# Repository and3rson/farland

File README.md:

# farland
65C816-based single-board computer

# Schematic

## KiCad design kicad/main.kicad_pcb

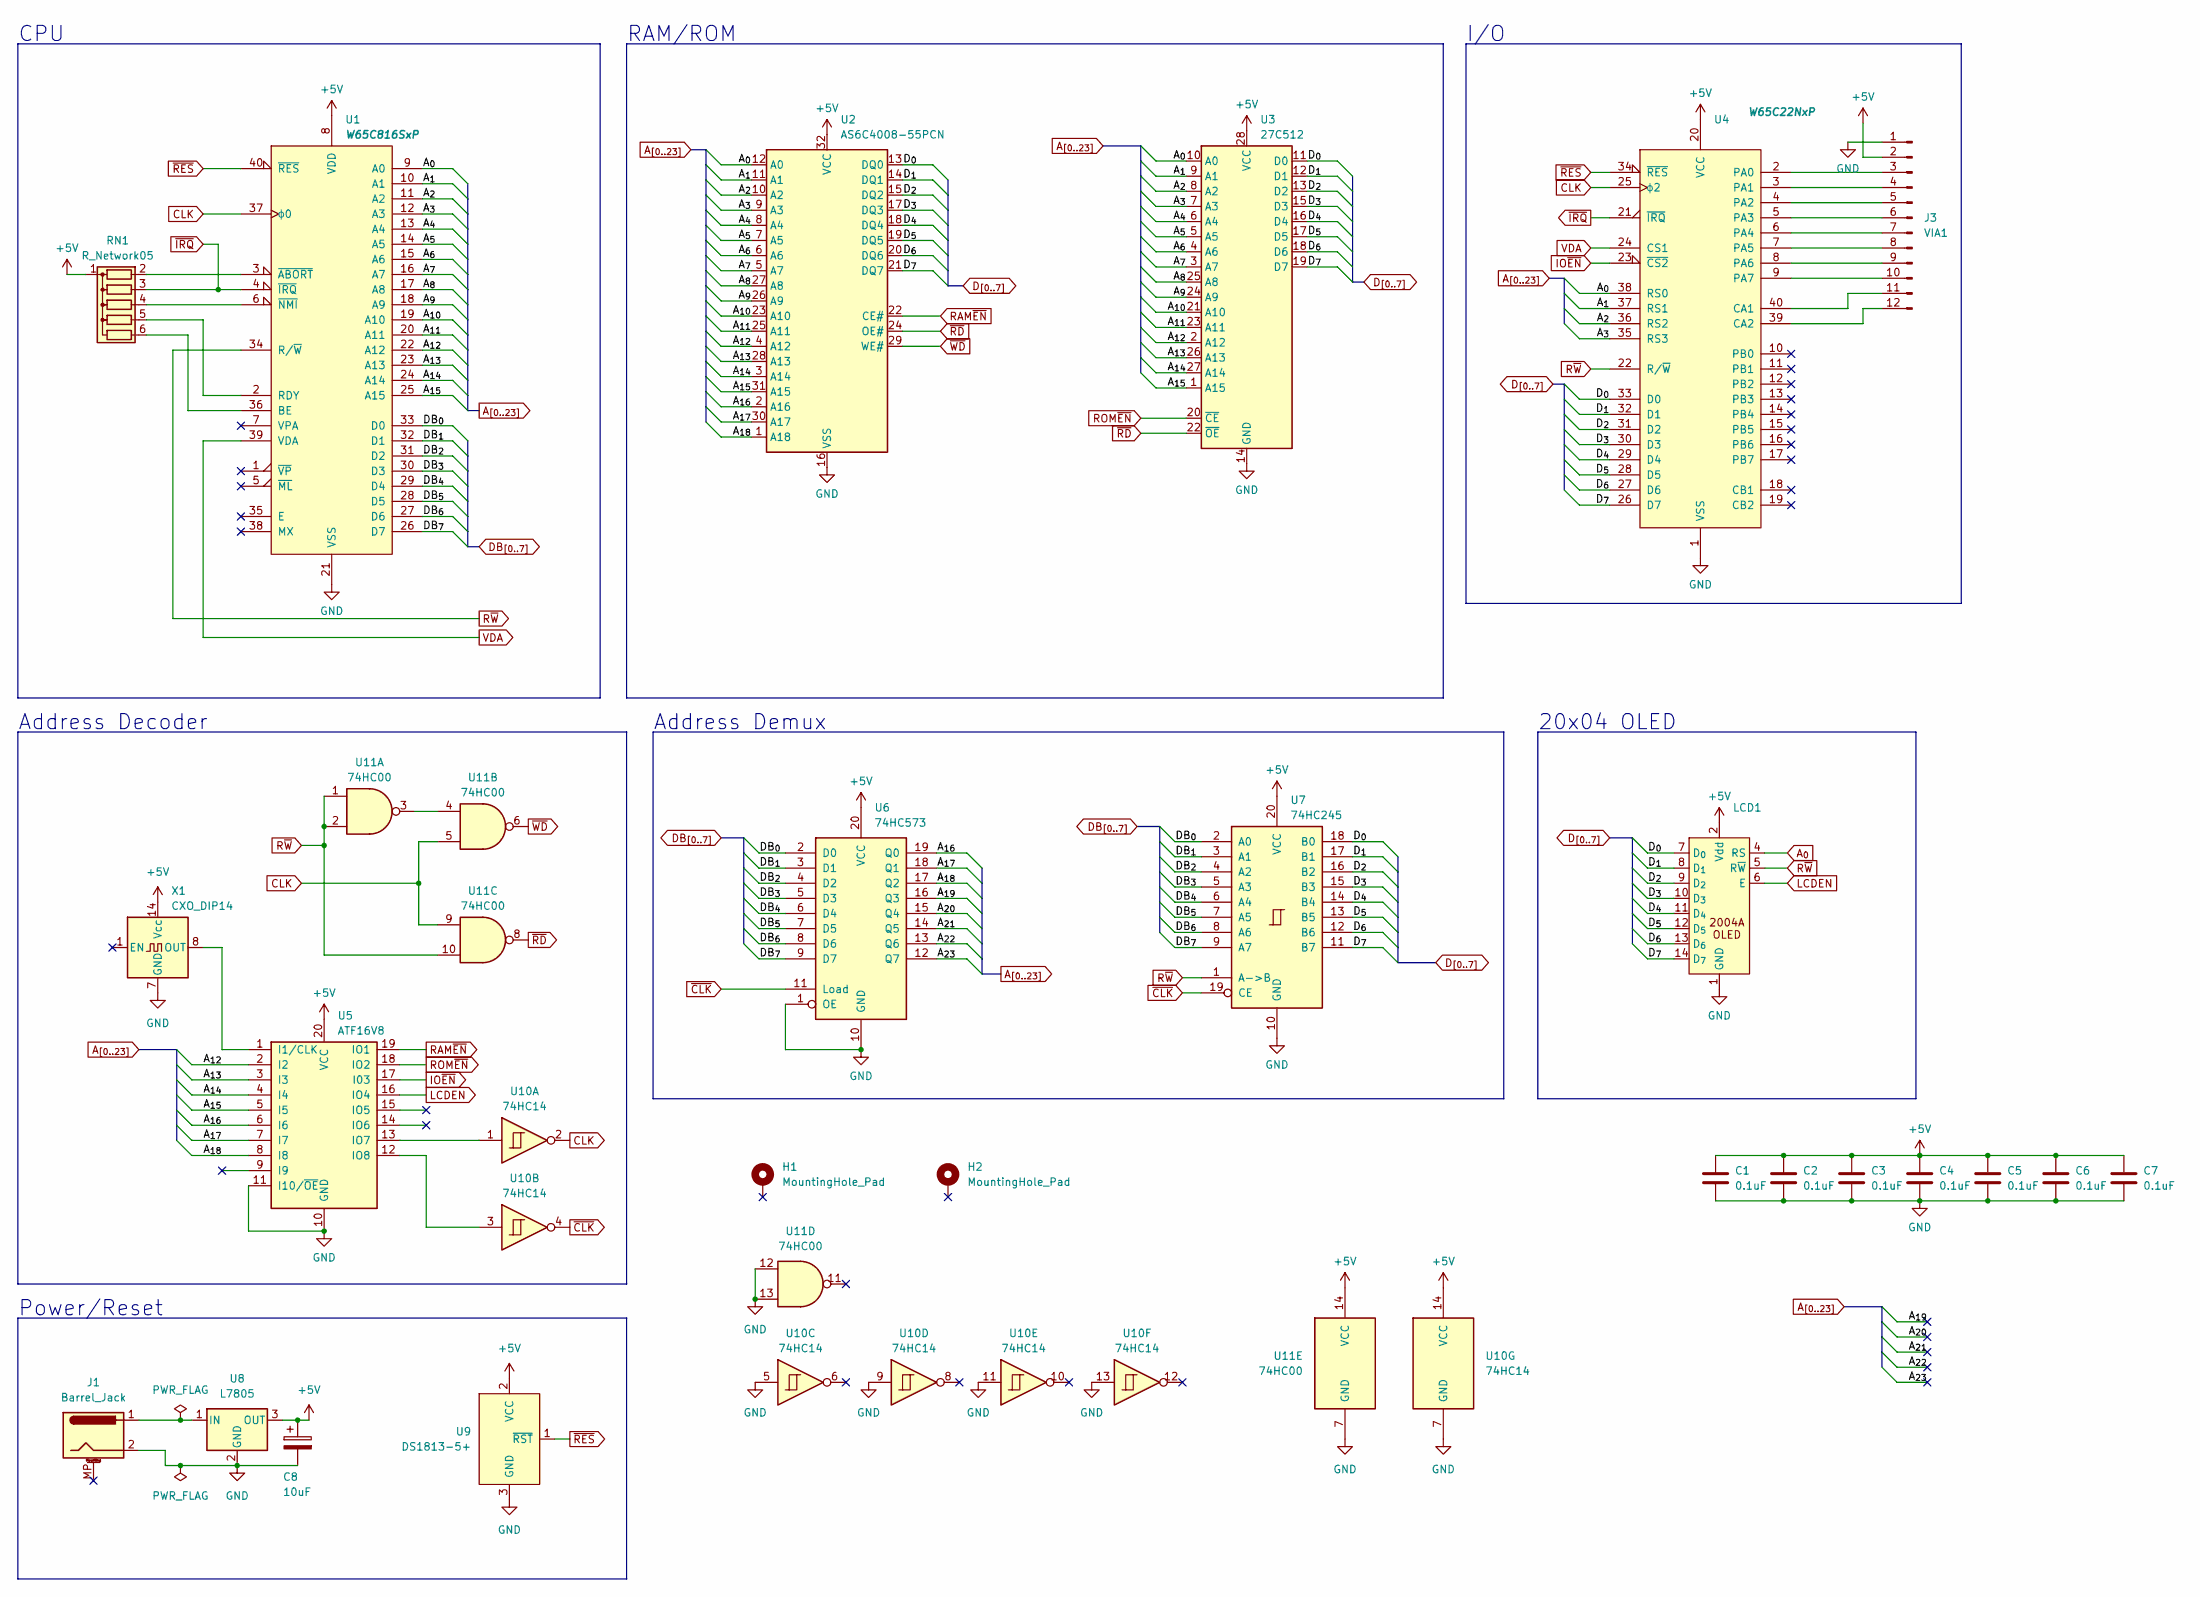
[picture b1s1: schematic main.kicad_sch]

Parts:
C1: 0.1uF; C_Disc_D3.0mm_W1.6mm_P2.50mm
C2, C3, C4: 0.1uF; C_Disc_VeryLong
C5, C6, C7: 0.1uF; C_Disc_Long
C8: 10uF; CP_Radial_D6.3mm_P2.50mm
H1, H2: MountingHole_Pad; MountingHole_2.5mm_Pad
J1: Barrel_Jack; BarrelJack_Wuerth_6941xx301002
J3: VIA1; PinHeader_1x12_P2.54mm_Vertical
LCD1: 2004A-OLED
RN1: R_Network05; R_Array_SIP6
U1: W65C816SxP; DIP-40_W15.24mm_Socket
U2: AS6C4008-55PCN; DIP-32_W15.24mm_Socket
U3: 27C512; ZIF28
U4: W65C22NxP; DIP-40_W15.24mm_Socket
U5: ATF16V8; DIP-20_W7.62mm_Socket
U6: 74HC573; DIP-20_W7.62mm_Socket
U7: 74HC245; DIP-20_W7.62mm_Socket
U8: L7805; TO-220-3_Vertical
U9: DS1813-5+; TO-92
U10: 74HC14; DIP-14_W7.62mm_Socket
U11: 74HC00; DIP-14_W7.62mm_Socket
X1: CXO_DIP14; Oscillator_DIP-14

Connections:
+5V: C1.1, C2.1, C3.1, C4.1, C5.1, C6.1, C7.1, C8.1, J3.2, LCD1.2 (Vdd), RN1.1 (common), U1.8 (VDD), U2.32 (VCC), U3.28 (VCC), U4.20 (VCC), U5.20 (VCC), U6.20 (VCC), U7.20 (VCC), U8.3 (OUT), U9.2 (VCC), U10.14 (VCC), U11.14 (VCC), X1.14 (Vcc)
A_{0}: LCD1.4 (RS), U1.9 (A0), U2.12 (A0), U3.10 (A0), U4.38 (RS0)
A_{1}: U1.10 (A1), U2.11 (A1), U3.9 (A1), U4.37 (RS1)
A_{2}: U1.11 (A2), U2.10 (A2), U3.8 (A2), U4.36 (RS2)
A_{3}: U1.12 (A3), U2.9 (A3), U3.7 (A3), U4.35 (RS3)
A_{4}: U1.13 (A4), U2.8 (A4), U3.6 (A4)
A_{5}: U1.14 (A5), U2.7 (A5), U3.5 (A5)
A_{6}: U1.15 (A6), U2.6 (A6), U3.4 (A6)
A_{7}: U1.16 (A7), U2.5 (A7), U3.3 (A7)
A_{8}: U1.17 (A8), U2.27 (A8), U3.25 (A8)
A_{9}: U1.18 (A9), U2.26 (A9), U3.24 (A9)
A_{10}: U1.19 (A10), U2.23 (A10), U3.21 (A10)
A_{11}: U1.20 (A11), U2.25 (A11), U3.23 (A11)
A_{12}: U1.22 (A12), U2.4 (A12), U3.2 (A12), U5.2 (I2)
A_{13}: U1.23 (A13), U2.28 (A13), U3.26 (A13), U5.3 (I3)
A_{14}: U1.24 (A14), U2.3 (A14), U3.27 (A14), U5.4 (I4)
A_{15}: U1.25 (A15), U2.31 (A15), U3.1 (A15), U5.5 (I5)
A_{16}: U2.2 (A16), U5.6 (I6), U6.19 (Q0)
A_{17}: U2.30 (A17), U5.7 (I7), U6.18 (Q1)
A_{18}: U2.1 (A18), U5.8 (I8), U6.17 (Q2)
A_{19}: U6.16 (Q3)
A_{20}: U6.15 (Q4)
A_{21}: U6.14 (Q5)
A_{22}: U6.13 (Q6)
A_{23}: U6.12 (Q7)
CLK: U1.37 (ϕ0), U4.25 (ϕ2), U10.2, U11.5, U11.9
DB_{0}: U1.33 (D0), U6.2 (D0), U7.2 (A0)
DB_{1}: U1.32 (D1), U6.3 (D1), U7.3 (A1)
DB_{2}: U1.31 (D2), U6.4 (D2), U7.4 (A2)
DB_{3}: U1.30 (D3), U6.5 (D3), U7.5 (A3)
DB_{4}: U1.29 (D4), U6.6 (D4), U7.6 (A4)
DB_{5}: U1.28 (D5), U6.7 (D5), U7.7 (A5)
DB_{6}: U1.27 (D6), U6.8 (D6), U7.8 (A6)
DB_{7}: U1.26 (D7), U6.9 (D7), U7.9 (A7)
D_{0}: LCD1.7 (D_{0}), U2.13 (DQ0), U3.11 (D0), U4.33 (D0), U7.18 (B0)
D_{1}: LCD1.8 (D_{1}), U2.14 (DQ1), U3.12 (D1), U4.32 (D1), U7.17 (B1)
D_{2}: LCD1.9 (D_{2}), U2.15 (DQ2), U3.13 (D2), U4.31 (D2), U7.16 (B2)
D_{3}: LCD1.10 (D_{3}), U2.17 (DQ3), U3.15 (D3), U4.30 (D3), U7.15 (B3)
D_{4}: LCD1.11 (D_{4}), U2.18 (DQ4), U3.16 (D4), U4.29 (D4), U7.14 (B4)
D_{5}: LCD1.12 (D_{5}), U2.19 (DQ5), U3.17 (D5), U4.28 (D5), U7.13 (B5)
D_{6}: LCD1.13 (D_{6}), U2.20 (DQ6), U3.18 (D6), U4.27 (D6), U7.12 (B6)
D_{7}: LCD1.14 (D_{7}), U2.21 (DQ7), U3.19 (D7), U4.26 (D7), U7.11 (B7)
GND: C1.2, C2.2, C3.2, C4.2, C5.2, C6.2, C7.2, C8.2, J1.2, J3.1, LCD1.1 (GND), U1.21 (VSS), U2.16 (VSS), U3.14 (GND), U4.1 (VSS), U5.10 (GND), U5.11 (I10/~OE), U6.1 (OE), U6.10 (GND), U7.10 (GND), U8.2 (GND), U9.3 (GND), U10.5, U10.7 (GND), U10.9, U10.11, U10.13, U11.7 (GND), U11.12, U11.13, X1.7 (GND)
IO~EN: U4.23 (~CS2), U5.17 (I03)
LCDEN: LCD1.6 (E), U5.16 (IO4)
unnamed: J3.3, U4.2 (PA0)
unnamed: J3.4, U4.3 (PA1)
unnamed: J3.5, U4.4 (PA2)
unnamed: J3.6, U4.5 (PA3)
unnamed: J3.7, U4.6 (PA4)
unnamed: J3.8, U4.7 (PA5)
unnamed: J3.9, U4.8 (PA6)
unnamed: J3.10, U4.9 (PA7)
unnamed: J3.11, U4.40 (CA1)
unnamed: J3.12, U4.39 (CA2)
unnamed: RN1.2 (R1), U1.3 (~ABORT)
unnamed: RN1.4 (R3), U1.6 (~NMI)
unnamed: RN1.5 (R4), U1.2 (RDY)
unnamed: RN1.6 (R5), U1.36 (BE)
unnamed: U5.1 (I1/CLK), X1.8 (OUT)
unnamed: U5.13 (IO7), U10.1
unnamed: U5.12 (IO8), U10.3
unnamed: J1.1, U8.1 (IN)
unnamed: U11.3, U11.4
RAM~EN: U2.22 (CE#), U5.19 (IO1)
ROM~EN: U3.20 (~CE), U5.18 (IO2)
R~W: LCD1.5 (R~W), U1.34 (R/~W), U4.22 (R/~W), U7.1 (A->B), U11.1, U11.2, U11.10
VDA: U1.39 (VDA), U4.24 (CS1)
~CLK: U6.11 (Load), U7.19 (CE), U10.4
~IRQ: RN1.3 (R2), U1.4 (~IRQ), U4.21 (~IRQ)
~RD: U2.24 (OE#), U3.22 (~OE), U11.8
~RES: U1.40 (~RES), U4.34 (~RES), U9.1 (~RST)
~WD: U2.29 (WE#), U11.6

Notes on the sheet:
Power/Reset
Address Decoder
20x04 OLED
CPU
Address Demux
I/O
RAM/ROM

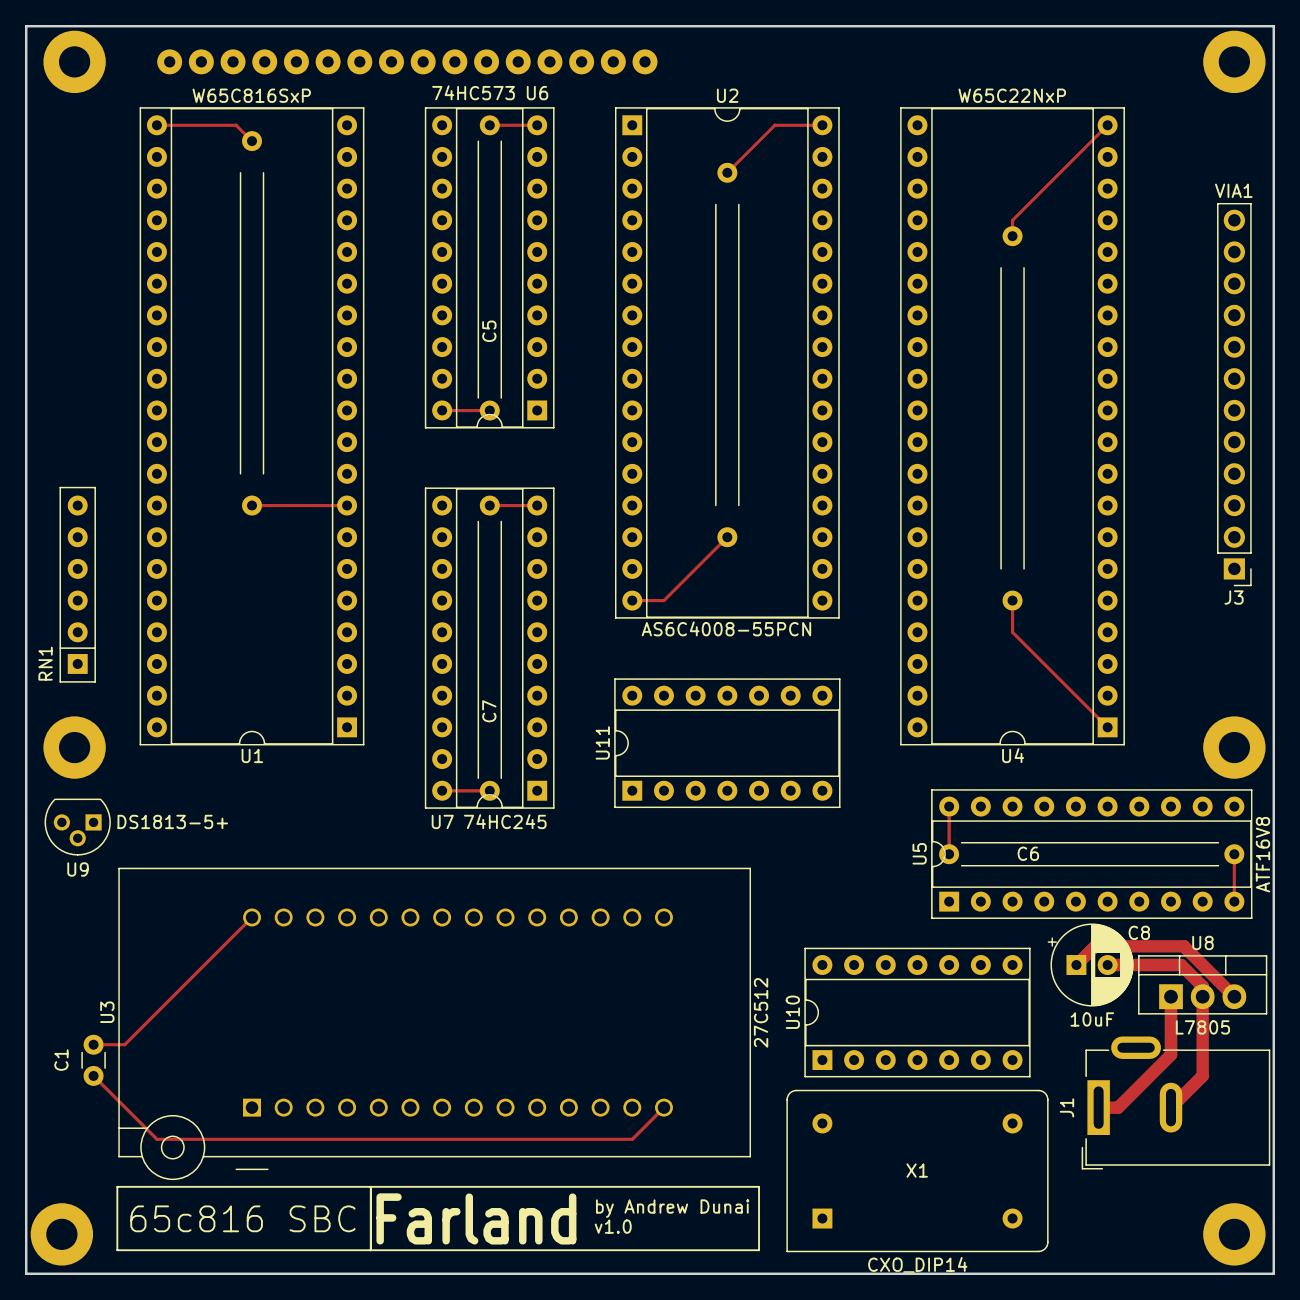
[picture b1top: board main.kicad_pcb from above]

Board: 2 copper layers, 100.0 x 100.0 mm, 26 parts (0 on the bottom side), 68 nets.

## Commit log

2023-08-27 Initial schematics
2023-08-30 v0.1 PCB
2023-08-30 v0.1 final PCB
2023-08-31 Add 74HC00 for R/W qualification to save ATF pins for slow mode
